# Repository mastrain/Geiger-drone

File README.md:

# Geiger-drone
This repository contains project code and schematics of a geiger sensor and its interface with Ardupilot.

Ardupilot refers to the Ardupilot project, an open-software drone flight controler : http://ardupilot.com/

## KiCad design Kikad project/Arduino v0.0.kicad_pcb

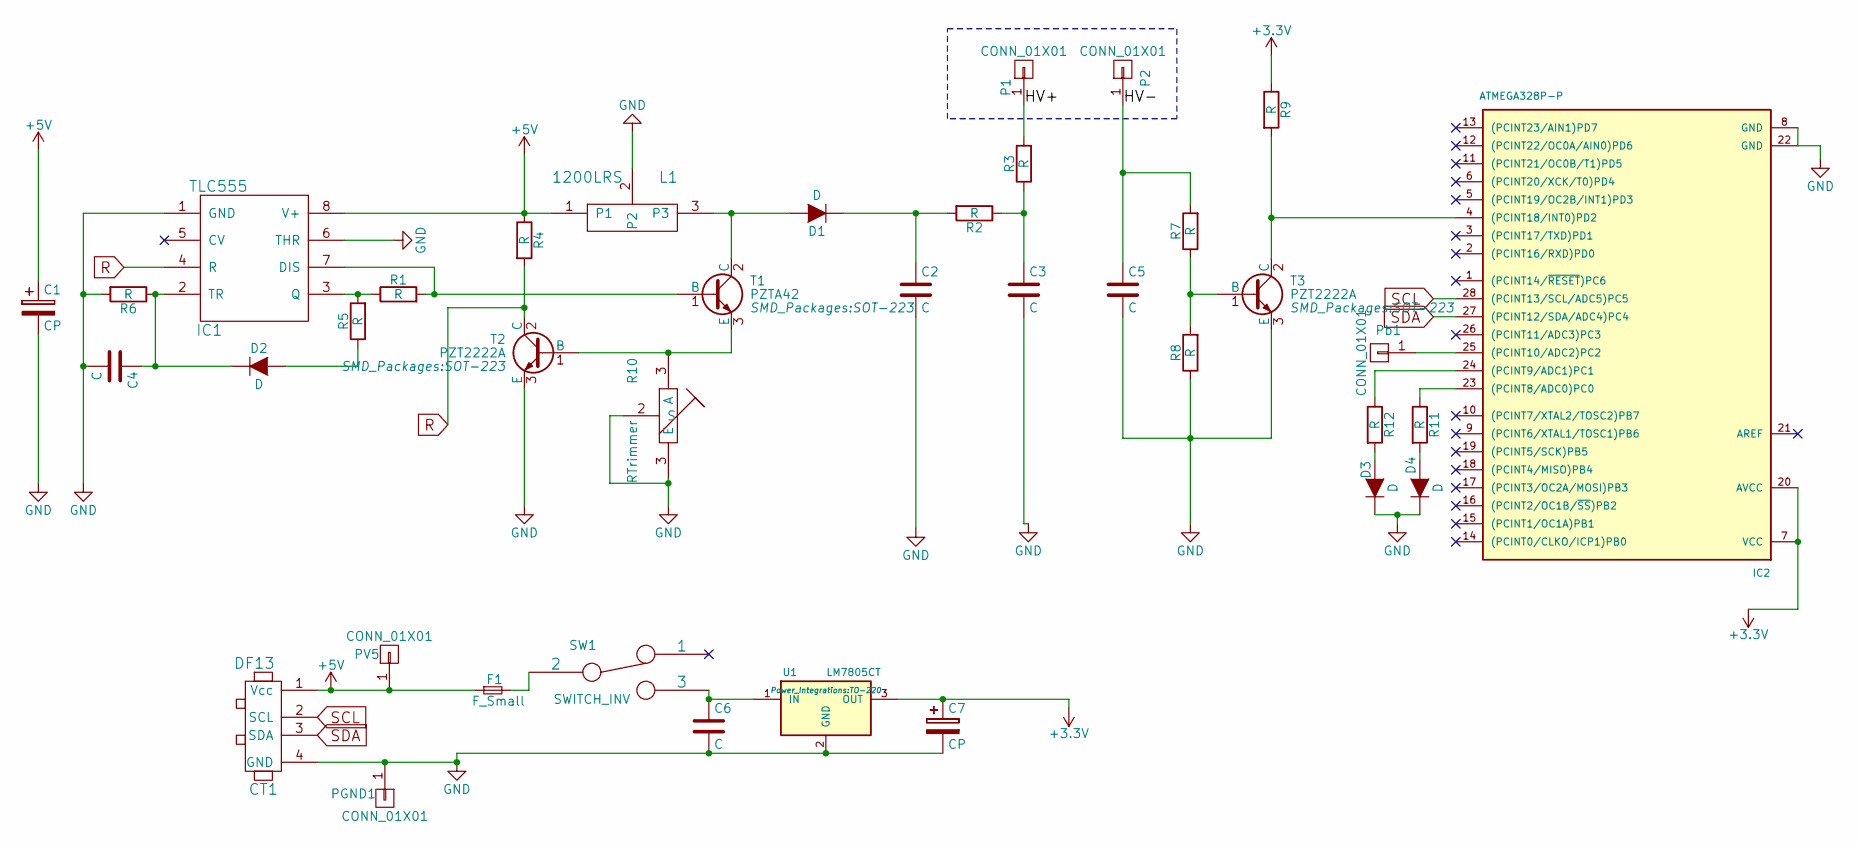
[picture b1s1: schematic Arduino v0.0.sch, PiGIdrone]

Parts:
C1: CP; c_elec_8x6.5
C2, C3: C; C_1206_HandSoldering
C4, C5: C; C_0805_HandSoldering
C6: C; C_Rect_L7_W2_P5
C7: CP; C_Radial_D5_L11_P2
CT1: DF13; df13-4p-125h
D1: D; Diode-SMA_Handsoldering
D2: D; SOD-123
D3, D4: D; LED-3MM
F1: F_Small; Fuseholder5x20_horiz_SemiClosed_Casing10x25mm
IC1: TLC555; SOIC-8-N
IC2: ATMEGA328P-P; dil_28-300_socket
L1: 1200LRS; Inductor_Circular_4_throuhole
P1, P2: CONN_01X01; Measurement_Point_Square-SMD-Pad_Big
PGND1: CONN_01X01; 1pin
PV5: CONN_01X01; 1pin
Pb1: CONN_01X01; 1pin
R1, R4, R5, R6, R7, R8, R9: R; R_0805_HandSoldering
R2, R3: R; R_1206_HandSoldering
R10: RTrimmer; trimmer_multivuelta
R11, R12: R; 7_5mm_drills
SW1: SWITCH_INV; Switch_3pin_2.54mm
T1: PZTA42; SOT-223
T2, T3: PZT2222A; SOT-223
U1: LM7805CT; TO-220

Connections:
+3V3: C7.1, IC2.7 (VCC), IC2.20 (AVCC), R9.1, U1.3 (OUT)
+5V: C1.1, CT1.1 (Vcc), F1.1, IC1.8 (V+), L1.1, PV5.1, R4.1
/HV+: P1.1, R3.2
/HV-: C5.1, P2.1, R7.2
unnamed: C2.1, D1.1 (K), R2.2
unnamed: C3.1, R2.1, R3.1
unnamed: C4.1, D2.1 (K), IC1.2 (TR), R6.1
unnamed: C6.1, SW1.3, U1.1 (IN)
unnamed: D1.2 (A), L1.3, T1.2 (C), T1.4
unnamed: D2.2 (A), R5.1
unnamed: D3.2 (A), R12.2
unnamed: D4.2 (A), R11.2
unnamed: F1.2, SW1.2
unnamed: IC1.3 (Q), R1.1, R5.2
unnamed: IC1.7 (DIS), R1.2, T1.1 (B)
unnamed: IC2.4 ((PCINT18/INT0)PD2), R9.2, T3.2 (C), T3.4
unnamed: IC2.23 ((PCINT8/ADC0)PC0), R11.1
unnamed: IC2.24 ((PCINT9/ADC1)PC1), R12.1
unnamed: IC2.25 ((PCINT10/ADC2)PC2), Pb1.1
unnamed: R7.1, R8.2, T3.1 (B)
R: IC1.4 (R), R4.2, T2.2 (C)
SCL: CT1.2 (SCL), IC2.28 ((PCINT13/SCL/ADC5)PC5)
SDA: CT1.3 (SDA), IC2.27 ((PCINT12/SDA/ADC4)PC4)

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
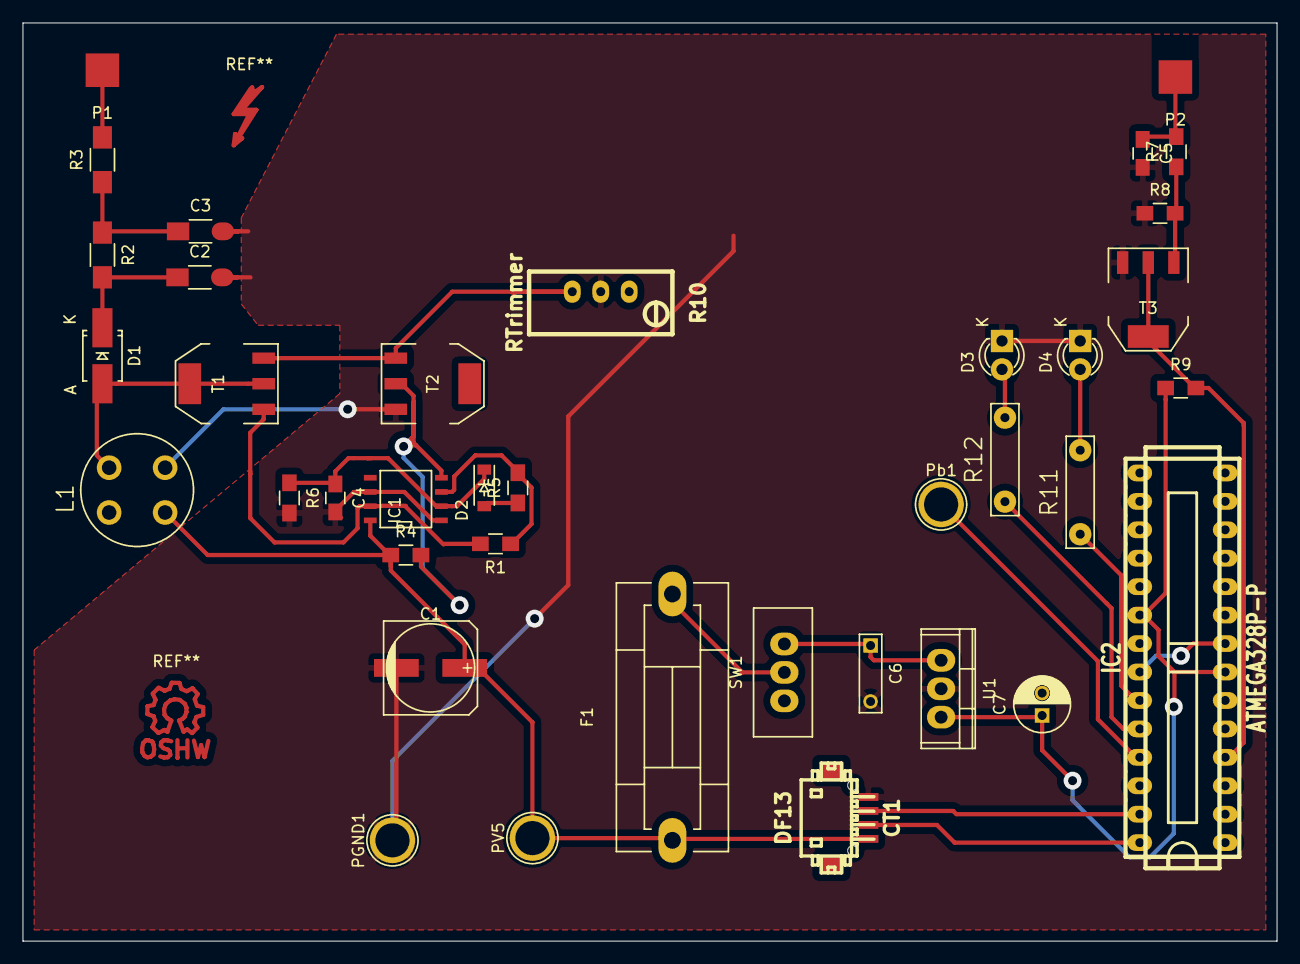
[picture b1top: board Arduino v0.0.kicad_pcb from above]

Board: 2 copper layers, 112.0 x 82.0 mm, 38 parts (0 on the bottom side), 25 nets.

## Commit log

2016-03-17 added readme
2016-03-17 All Ardupilot project is under GNU license
2016-03-17 Create LICENSE
2016-03-17 gitingore commit
2016-03-17 Added kikad project. Contains Arduino geiger board
